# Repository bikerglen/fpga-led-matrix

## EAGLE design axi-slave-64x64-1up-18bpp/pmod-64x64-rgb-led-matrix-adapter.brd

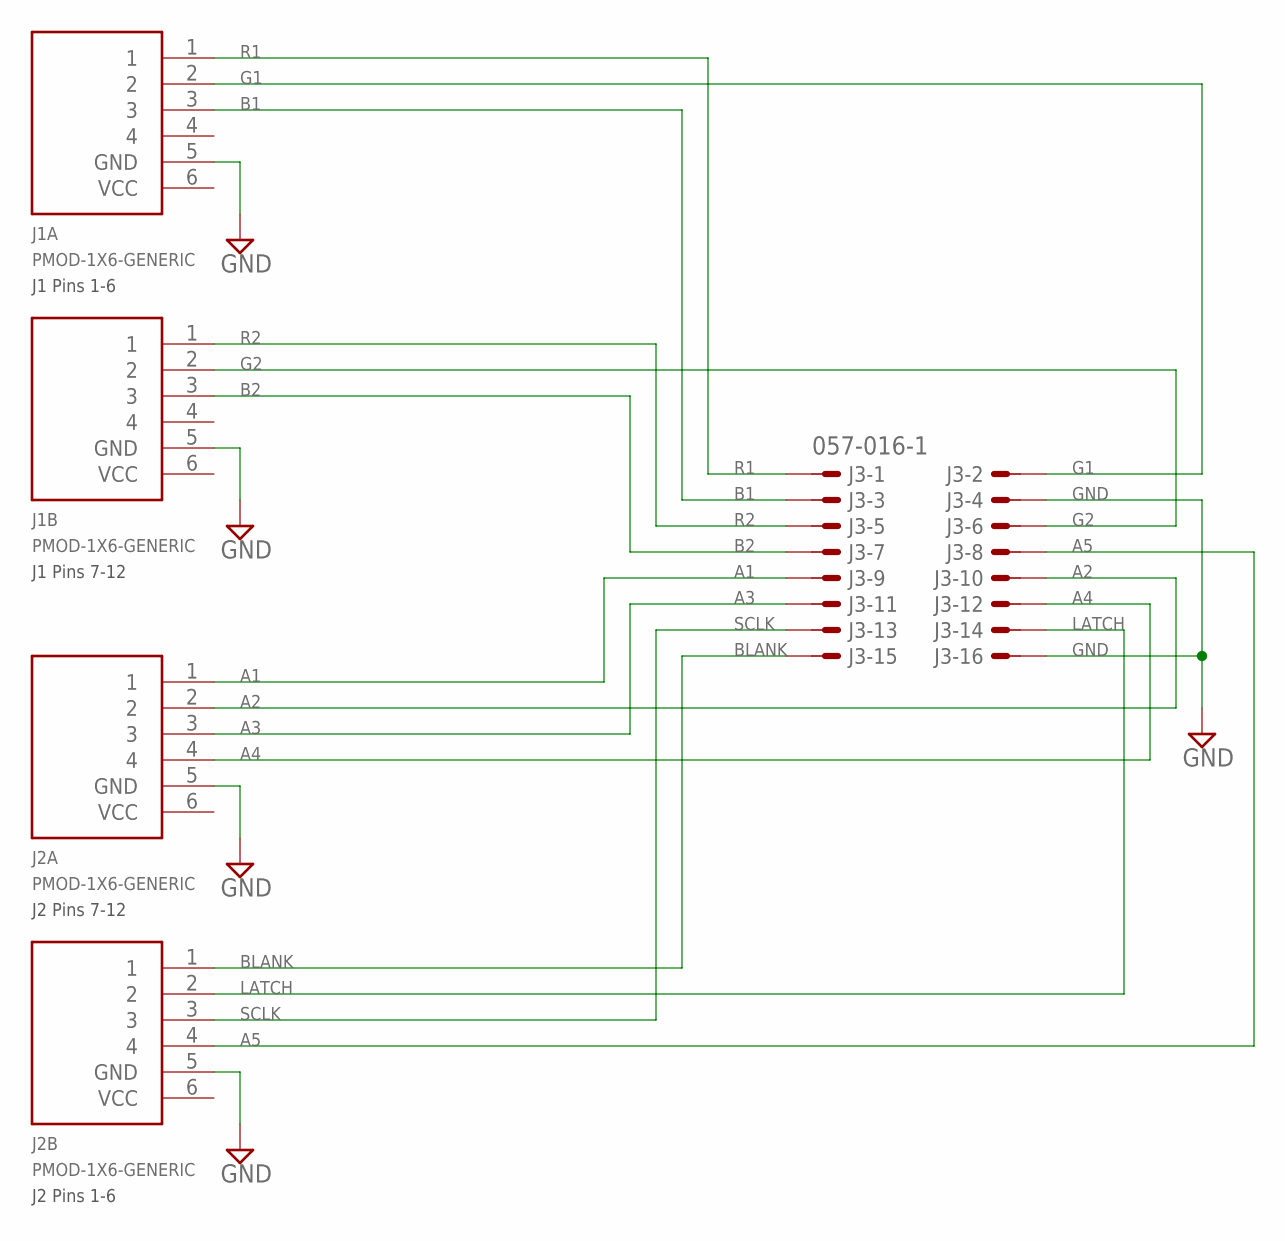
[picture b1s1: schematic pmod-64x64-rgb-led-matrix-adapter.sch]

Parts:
J1A, J1B, J2A, J2B: PMOD-1X6-GENERIC; CON-PMOD-1X6
J3: 057-016-1

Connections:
A1: J2A.1, J3.9
A2: J2A.2, J3.10
A3: J2A.3, J3.11
A4: J2A.4, J3.12
A5: J2B.4, J3.8
B1: J1A.3, J3.3
B2: J1B.3, J3.7
BLANK: J2B.1, J3.15
G1: J1A.2, J3.2
G2: J1B.2, J3.6
GND: J1A.5 (GND), J1B.5 (GND), J2A.5 (GND), J2B.5 (GND), J3.4, J3.16
LATCH: J2B.2, J3.14
R1: J1A.1, J3.1
R2: J1B.1, J3.5
SCLK: J2B.3, J3.13

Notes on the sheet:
J1 Pins 7-12
J1 Pins 1-6
J2 Pins 1-6
J2 Pins 7-12

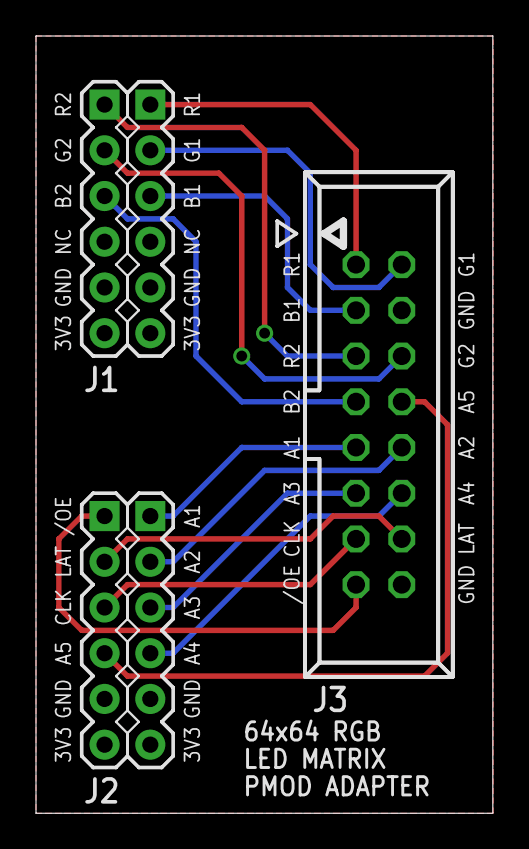
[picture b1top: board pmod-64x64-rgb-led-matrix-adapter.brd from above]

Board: 2 copper layers, 25.4 x 43.2 mm, 5 parts (0 on the bottom side), 15 nets.

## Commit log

2017-12-21 initial checkin
2018-01-20 added async clock group
2018-01-20 initial checkin of 64x64 1up 18bpp rtl and xdc
2018-01-20 added xci files for DPRAMs
2018-01-20 c code for zybo and minized w/ 1up 64x64 18bpp matrix driver
2018-01-21 add pmod adapter board to connect minized/arty/zybo to display ribbon cable
